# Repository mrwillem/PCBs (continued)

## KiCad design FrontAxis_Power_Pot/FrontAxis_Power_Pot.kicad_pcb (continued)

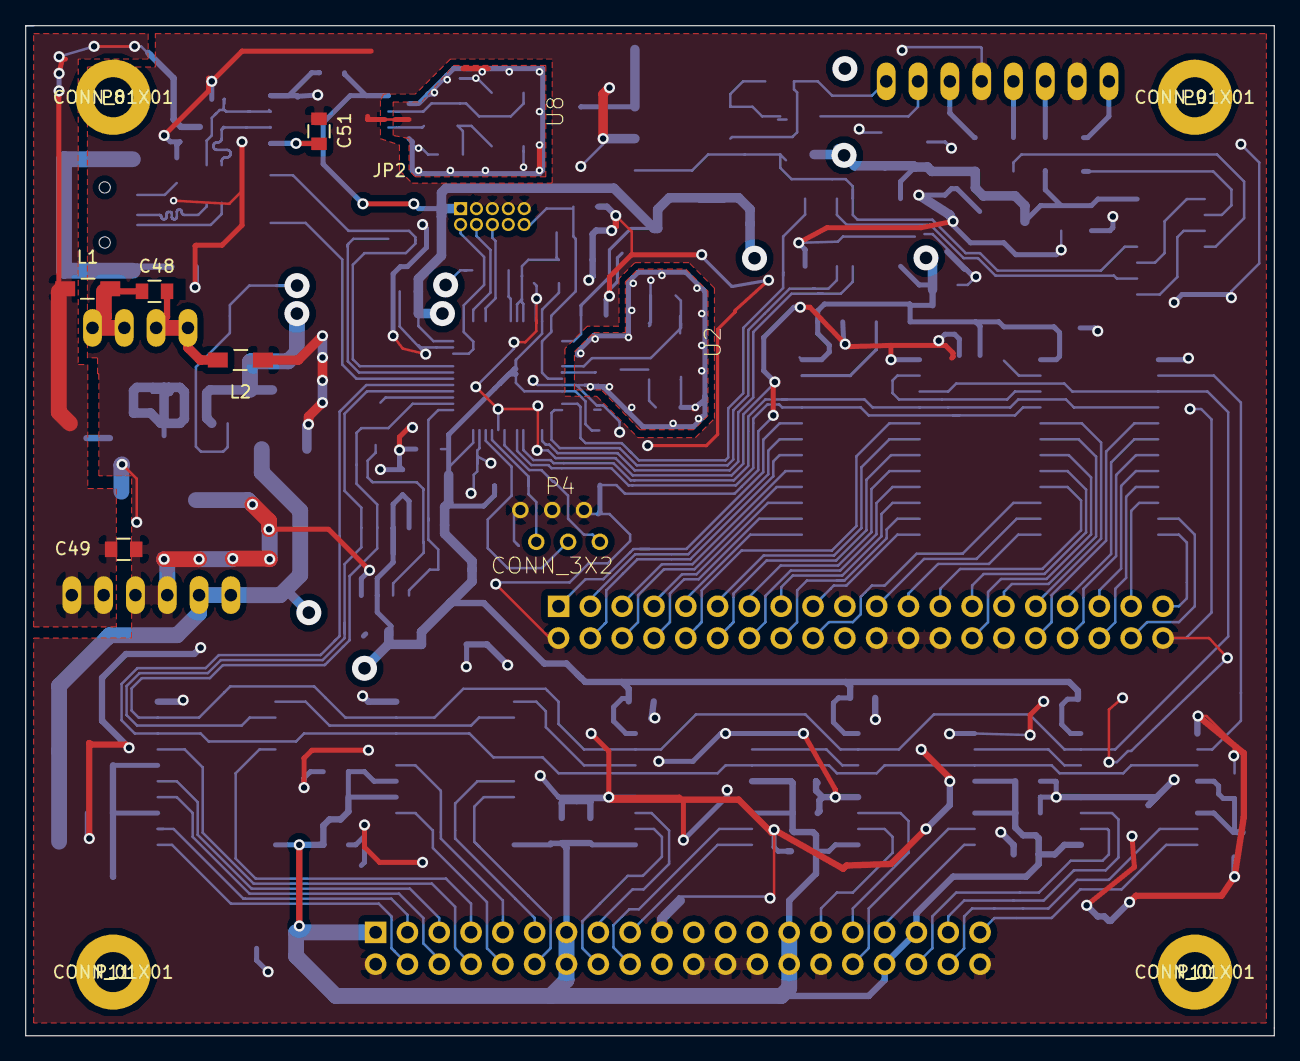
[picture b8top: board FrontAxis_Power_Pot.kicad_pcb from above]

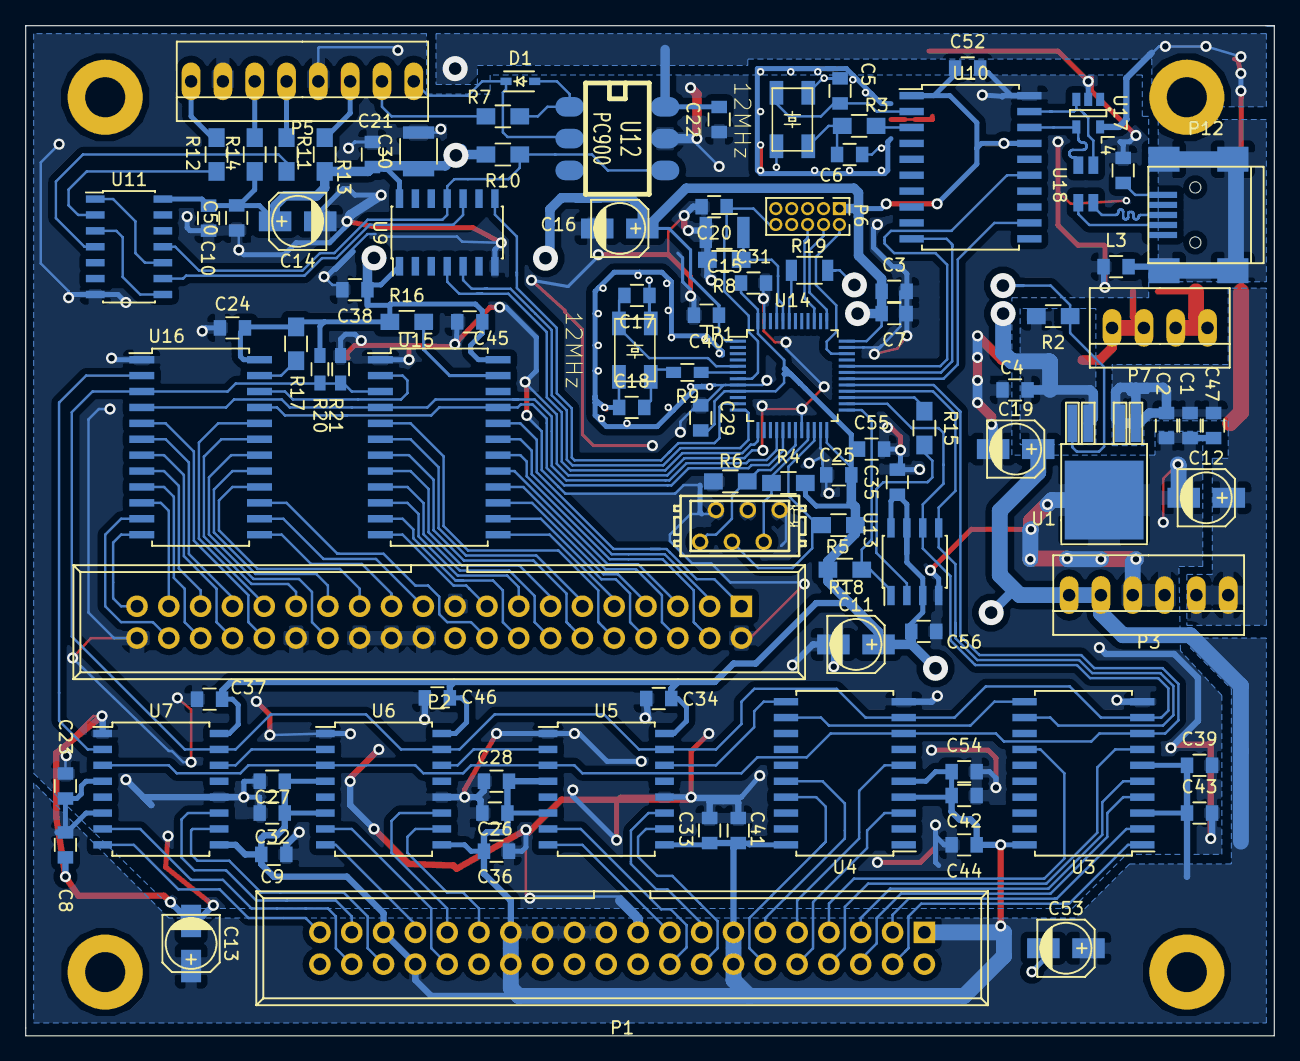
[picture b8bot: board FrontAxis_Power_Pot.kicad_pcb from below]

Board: 4 copper layers, 99.7 x 80.6 mm, 113 parts (103 on the bottom side), 119 nets.
